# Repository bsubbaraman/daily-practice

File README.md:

### daily practice archive

to use templates for making new posts:
- installation:
  - make a virtual environment, `python3 -m venv .venv && source .venv/bin/activate`
  - install jinja2, `python3 -m pip install jinja2`
- usage:
  - `post_setup.py <YYYY> <MM> <DD> <post_title>`

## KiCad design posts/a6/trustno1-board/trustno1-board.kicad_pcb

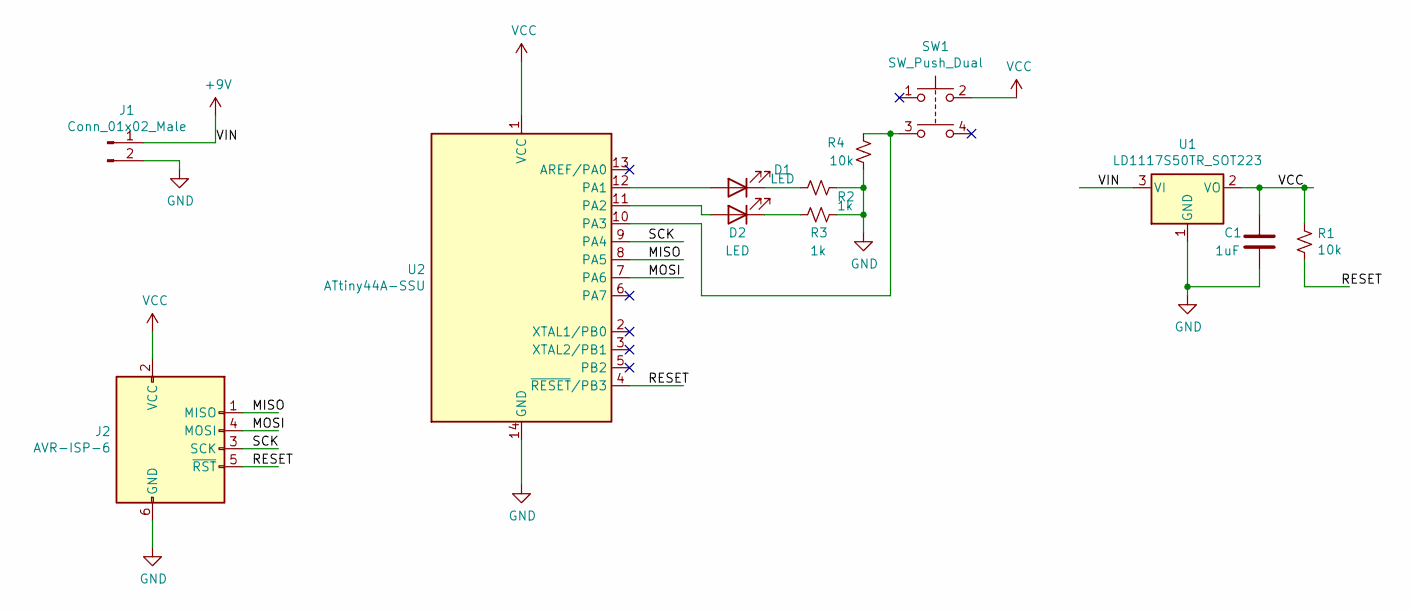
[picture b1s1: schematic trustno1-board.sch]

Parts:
C1: 1uF; C_1206_3216Metric_Pad1.33x1.80mm_HandSolder
D1, D2: LED; LED_1206_3216Metric
J1: Conn_01x02_Male; PinHeader_1x02_P2.54mm_Vertical
J2: AVR-ISP-6; PinHeader_2x03_P2.54mm_Vertical_SMD
R1, R4: 10k; R_1206_3216Metric_Pad1.30x1.75mm_HandSolder
R2, R3: 1k; R_1206_3216Metric_Pad1.30x1.75mm_HandSolder
SW1: SW_Push_Dual; Omron-B3SN-3112P-MFG
U1: LD1117S50TR_SOT223; SOT-223-3_TabPin2
U2: ATtiny44A-SSU; SOIC-14_3.9x8.7mm_P1.27mm

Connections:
+9V: J1.1, U1.3 (VI)
/MISO: J2.1 (MISO), U2.8 (PA5)
/MOSI: J2.4 (MOSI), U2.7 (PA6)
/RESET: J2.5 (~RST), R1.2, U2.4 (~RESET~/PB3)
/SCK: J2.3 (SCK), U2.9 (PA4)
GND: C1.2, J1.2, J2.6 (GND), R2.1, R3.1, R4.1, U1.1 (GND), U2.14 (GND)
unnamed: D1.1 (K), R2.2
unnamed: D1.2 (A), U2.12 (PA1)
unnamed: D2.1 (K), R3.2
unnamed: D2.2 (A), U2.11 (PA2)
unnamed: R4.2, SW1.3, U2.10 (PA3)
VCC: C1.1, J2.2 (VCC), R1.1, SW1.2, U1.2 (VO), U2.1 (VCC)

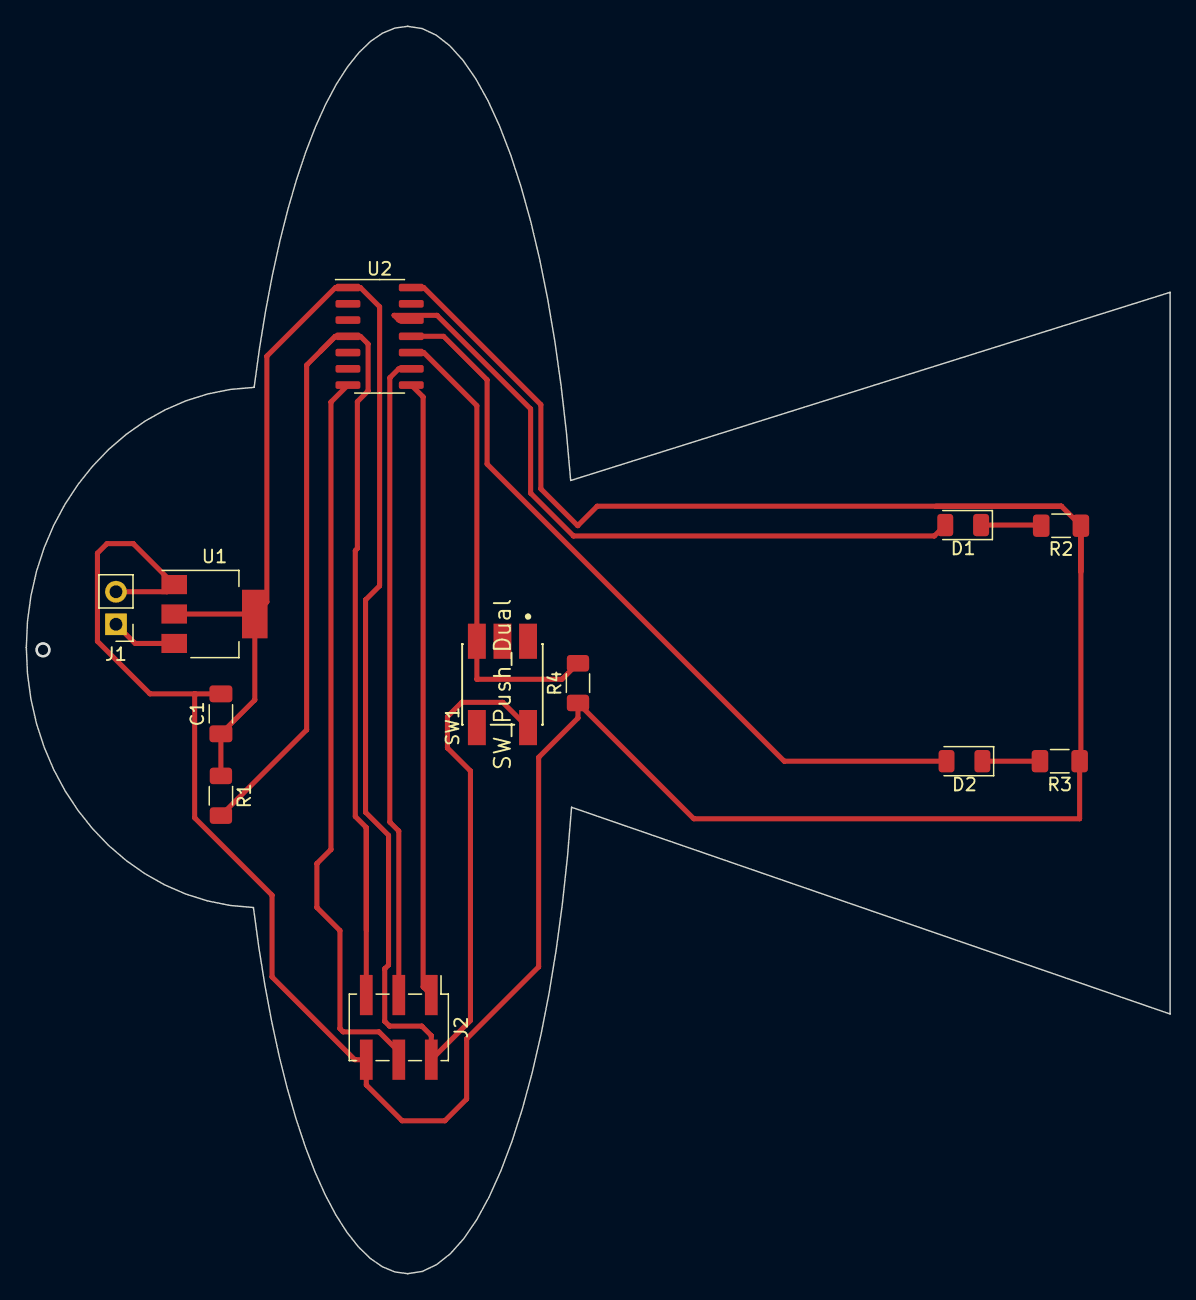
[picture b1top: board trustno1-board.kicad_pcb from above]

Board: 2 copper layers, 89.4 x 97.5 mm, 12 parts (0 on the bottom side), 12 nets.

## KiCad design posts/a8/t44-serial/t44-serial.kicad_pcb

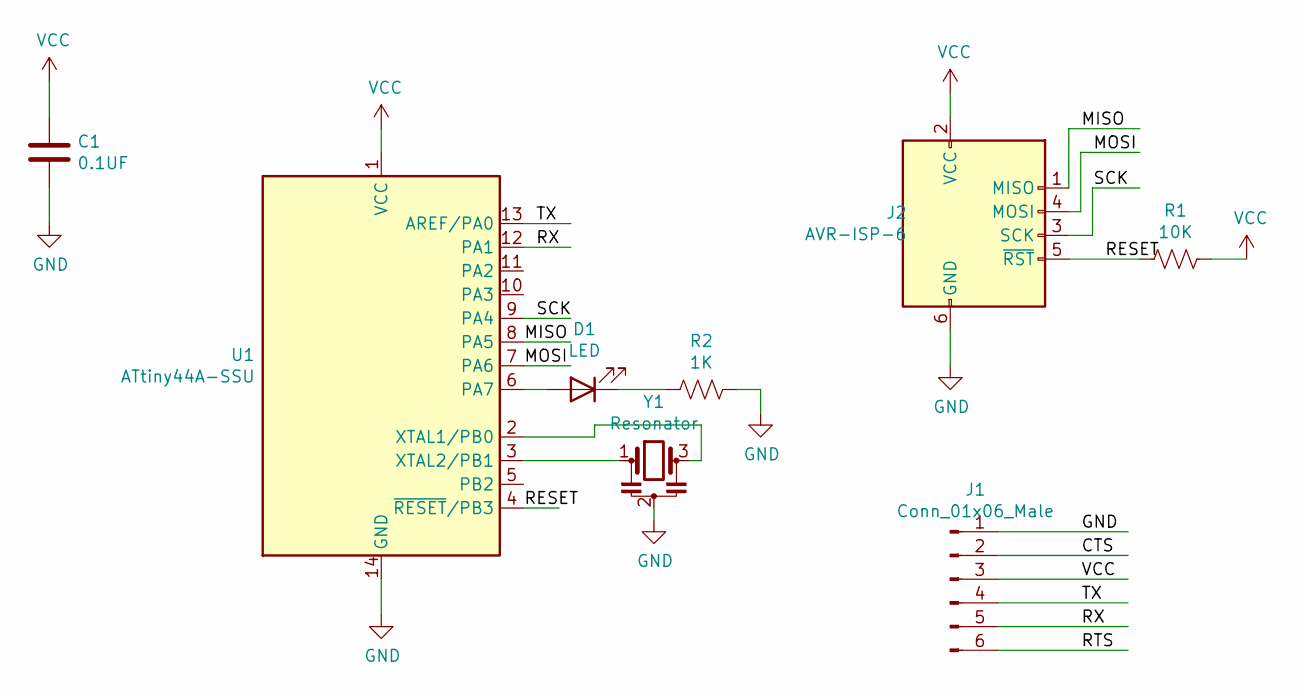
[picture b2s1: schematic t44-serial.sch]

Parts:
C1: 0.1UF; C_1206_3216Metric
D1: LED; LED_1206_3216Metric
J1: Conn_01x06_Male; PinHeader_1x06_P2.54mm_Horizontal
J2: AVR-ISP-6; PinHeader_2x03_P2.54mm_Vertical_SMD
R1: 10K; R_1206_3216Metric
R2: 1K; R_1206_3216Metric
U1: ATtiny44A-SSU; SOIC-14_3.9x8.7mm_P1.27mm
Y1: Resonator; Resonator_SMD_muRata_CSTxExxV-3Pin_3.0x1.1mm_HandSoldering

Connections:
/CTS: J1.2
/MISO: J2.1 (MISO), U1.8 (PA5)
/MOSI: J2.4 (MOSI), U1.7 (PA6)
/RESET: J2.5 (~RST), R1.2, U1.4 (~RESET~/PB3)
/RTS: J1.6
/RX: J1.5, U1.12 (PA1)
/SCK: J2.3 (SCK), U1.9 (PA4)
/TX: J1.4, U1.13 (AREF/PA0)
GND: C1.2, J1.1, J2.6 (GND), R2.1, U1.14 (GND), Y1.2
unnamed: D1.1 (K), R2.2
unnamed: D1.2 (A), U1.6 (PA7)
unnamed: U1.2 (XTAL1/PB0), Y1.3
unnamed: U1.3 (XTAL2/PB1), Y1.1
VCC: C1.1, J1.3, J2.2 (VCC), R1.1, U1.1 (VCC)

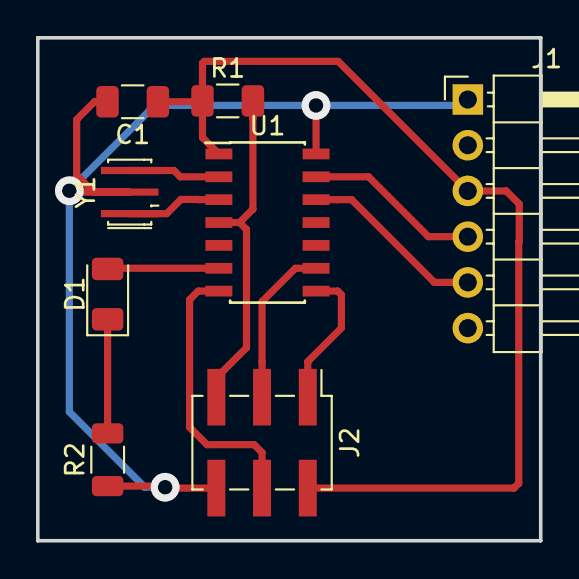
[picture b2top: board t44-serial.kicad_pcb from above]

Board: 2 copper layers, 27.9 x 27.9 mm, 8 parts (0 on the bottom side), 12 nets.

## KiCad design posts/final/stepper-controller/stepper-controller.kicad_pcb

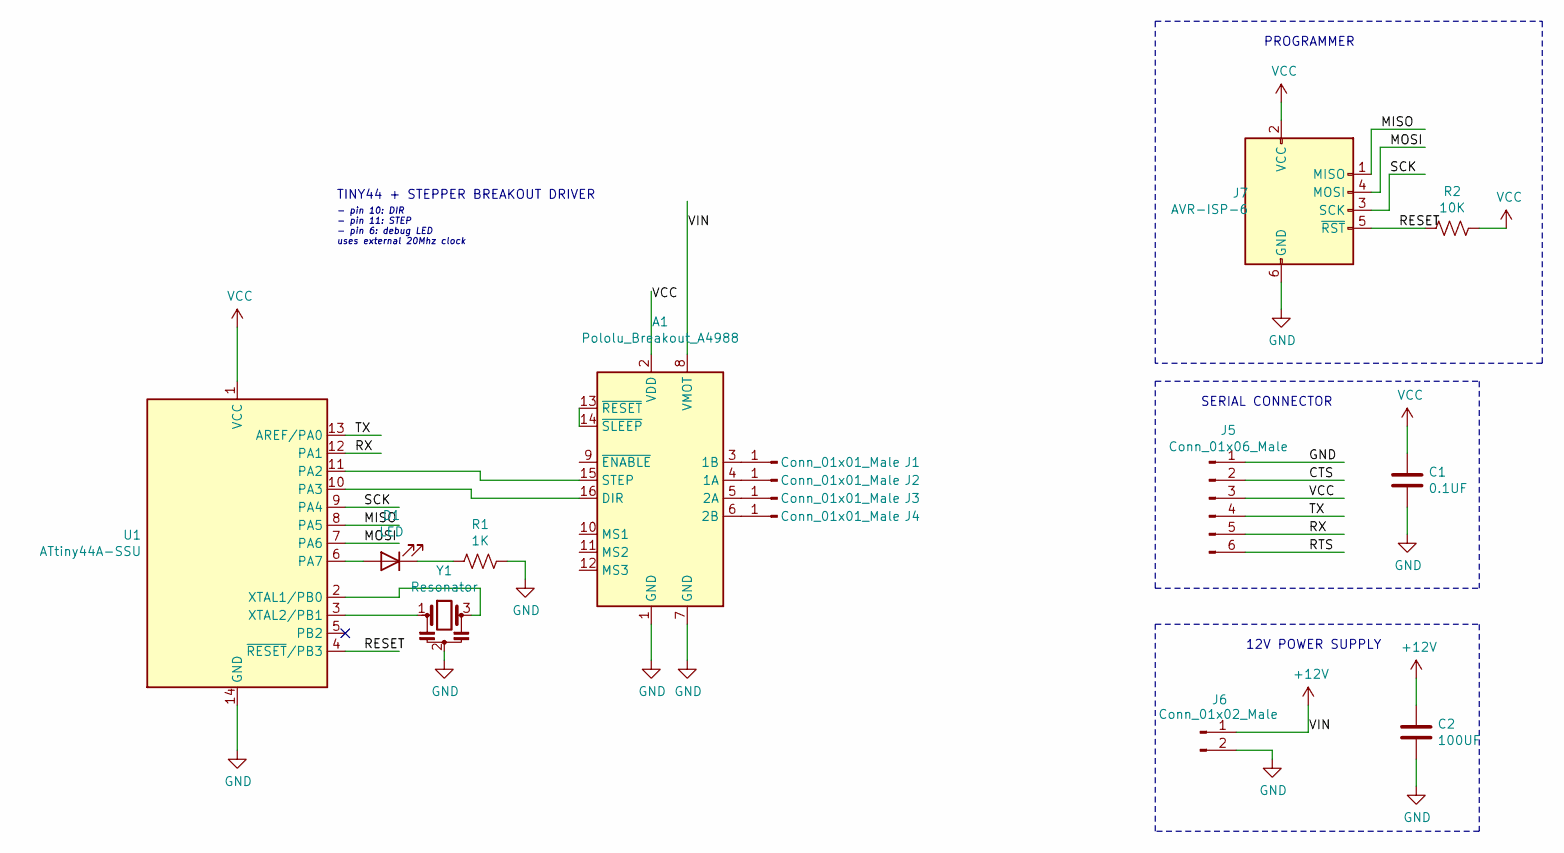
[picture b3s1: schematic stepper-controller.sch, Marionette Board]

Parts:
A1: Pololu_Breakout_A4988; Pololu_Breakout-16_15.2x20.3mm
C1: 0.1UF; C_1206_3216Metric
C2: 100UF; C_Elec_10x10.2
D1: LED; LED_1206_3216Metric
J1, J2, J3, J4: Conn_01x01_Male; PinHeader_1x01_P2.54mm_Vertical
J5: Conn_01x06_Male; PinHeader_1x06_P2.54mm_Horizontal
J6: Conn_01x02_Male; PinHeader_1x02_P2.54mm_Vertical
J7: AVR-ISP-6; PinHeader_2x03_P2.54mm_Vertical_SMD
R1: 1K; R_1206_3216Metric
R2: 10K; R_1206_3216Metric
U1: ATtiny44A-SSU; SOIC-14_3.9x8.7mm_P1.27mm
Y1: Resonator; Resonator_SMD_muRata_CSTxExxV-3Pin_3.0x1.1mm_HandSoldering

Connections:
+12V: A1.8 (VMOT), C2.1, J6.1
/CTS: J5.2
/MISO: J7.1 (MISO), U1.8 (PA5)
/MOSI: J7.4 (MOSI), U1.7 (PA6)
/RESET: J7.5 (~RST), R2.2, U1.4 (~RESET~/PB3)
/RTS: J5.6
/RX: J5.5, U1.12 (PA1)
/SCK: J7.3 (SCK), U1.9 (PA4)
/TX: J5.4, U1.13 (AREF/PA0)
GND: A1.1 (GND), A1.7 (GND), C1.2, C2.2, J5.1, J6.2, J7.6 (GND), R1.1, U1.14 (GND), Y1.2
unnamed: A1.3 (1B), J1.1
unnamed: A1.4 (1A), J2.1
unnamed: A1.5 (2A), J3.1
unnamed: A1.6 (2B), J4.1
unnamed: A1.13 (~RESET), A1.14 (~SLEEP)
unnamed: A1.15 (STEP), U1.11 (PA2)
unnamed: A1.16 (DIR), U1.10 (PA3)
unnamed: D1.1 (K), R1.2
unnamed: D1.2 (A), U1.6 (PA7)
unnamed: U1.2 (XTAL1/PB0), Y1.3
unnamed: U1.3 (XTAL2/PB1), Y1.1
VCC: A1.2 (VDD), C1.1, J5.3, J7.2 (VCC), R2.1, U1.1 (VCC)

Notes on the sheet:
PROGRAMMER
SERIAL CONNECTOR
12V POWER SUPPLY
TINY44 + STEPPER BREAKOUT DRIVER
- pin 10: DIR - pin 11: STEP - pin 6: debug LED uses external 20Mhz clock

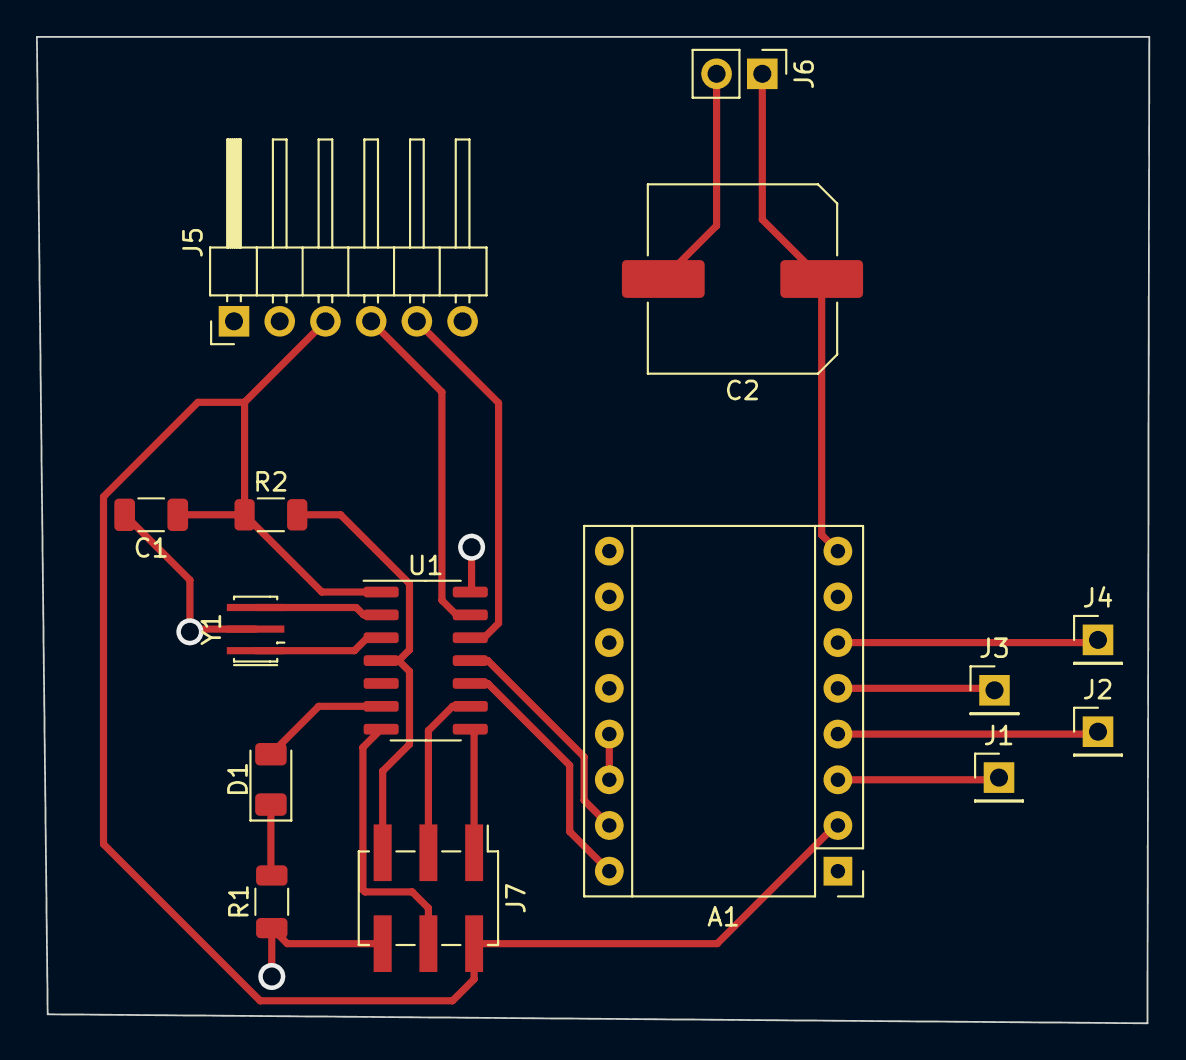
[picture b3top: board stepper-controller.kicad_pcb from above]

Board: 2 copper layers, 61.8 x 54.8 mm, 15 parts (0 on the bottom side), 20 nets.

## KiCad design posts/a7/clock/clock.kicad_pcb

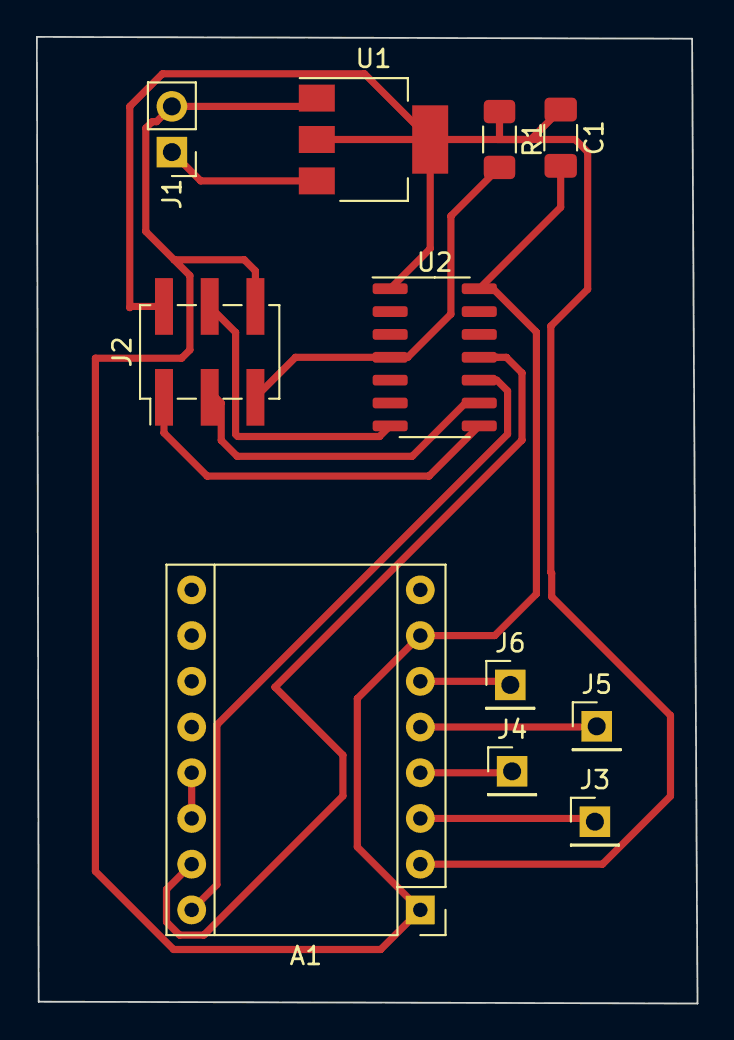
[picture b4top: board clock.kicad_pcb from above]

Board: 2 copper layers, 36.7 x 53.7 mm, 11 parts (0 on the bottom side), 14 nets.

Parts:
A1: Pololu_Breakout_A4988; Pololu_Breakout-16_15.2x20.3mm
C1: 1uF; C_1206_3216Metric_Pad1.33x1.80mm_HandSolder
J1: Conn_01x02_Male; PinHeader_1x02_P2.54mm_Vertical
J2: AVR-ISP-6; PinHeader_2x03_P2.54mm_Vertical_SMD
J3, J4, J5, J6: Conn_01x01_Male; PinHeader_1x01_P2.54mm_Vertical
R1: 10k; R_1206_3216Metric_Pad1.30x1.75mm_HandSolder
U1: LD1117S50TR_SOT223; SOT-223-3_TabPin2
U2: ATtiny44A-SSU; SOIC-14_3.9x8.7mm_P1.27mm

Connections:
+9V: A1.8, J1.1, U1.3
/MISO: J2.1, U2.8
/MOSI: J2.4, U2.7
/RESET: J2.5, R1.2, U2.4
/SCK: J2.3, U2.9
GND: A1.1, A1.7, C1.2, J1.2, J2.6, U1.1, U2.14
unnamed: A1.3, J3.1
unnamed: A1.4, J4.1
unnamed: A1.5, J5.1
unnamed: A1.6, J6.1
unnamed: A1.13, A1.14
unnamed: A1.15, U2.11
unnamed: A1.16, U2.10
VCC: A1.2, C1.1, J2.2, R1.1, U1.2, U2.1

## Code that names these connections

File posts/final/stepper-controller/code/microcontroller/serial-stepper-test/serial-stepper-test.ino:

// Include the SoftwareSerial library to run serial on Attiny44
#include <SoftwareSerial.h>
#define bit_delay_time 8.5 // bit delay for 115200 with overhead

// Stepper Motor Setup
#define stepPin PA2
#define dirPin PA3
#define stepsPerRevolution 200

// some calibration definitions
#define minRightElbowAngle = 17 // degrees

// declare my serial ports 0 and 1 (RX, TX)
SoftwareSerial mySerial(PA0, PA1);

int value = 0; //store the reading in value
int currentPos = 0;
void setup() {
  mySerial.begin(115200); // set baud rate to 115200 bits per second
  pinMode(stepPin, OUTPUT);
  pinMode(dirPin, OUTPUT);
  CLKPR = (1 << CLKPCE);
  CLKPR = (0 << CLKPS3) | (0 << CLKPS2) | (0 << CLKPS1) | (0 << CLKPS0);
}

void loop() {
  while (1) {
    while (mySerial.available () > 0 ) {
      value = mySerial.parseInt();
      if (value > 0) { // this is here bc random 0s sent. need to fix.
        mySerial.println(value);
        step(value);
      }
    }
    delay(200);
  }
}

void step(int s) {
  int dir = 1;
  if (s < currentPos){
    // Set the spinning direction CCW:
    digitalWrite(dirPin, LOW);
    dir = -1;
  }
  else { // clockwise
    digitalWrite(dirPin, HIGH);
  }

  int stepsToMove = abs(s - currentPos);
  // Spin the stepper motor 1 revolution slowly:
  for (int i = 0; i < stepsToMove; i++) {
    // These four lines result in 1 step:
    digitalWrite(stepPin, HIGH);
    delayMicroseconds(500); // change to modify speed
    digitalWrite(stepPin, LOW);
    delayMicroseconds(500);
  }

  currentPos += dir * stepsToMove;
}

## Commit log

2022-09-08 init
2022-09-08 20220908
2022-09-08 add to index
2022-09-09 20220909 + remove old files
2022-09-10 add post templating
2022-09-10 automatic site index updates
2022-09-10 add prev|
2022-09-10 typos from last commit: added prev|next tags to post templates
2022-09-10 blarf; remove test items from table after adding templates
2022-09-10 20220910
2022-09-11 20220911
2022-09-11 202209011
2022-09-13 20220912
2022-09-14 20220913
2022-09-15 20220914
2022-09-20 20220915/16
2022-09-21 20220920
2022-09-22 20220921
